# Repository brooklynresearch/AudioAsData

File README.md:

Vibrotextiles
=============
This repo is for all hardware and firmware associated with the vibrotextiles.
This is still a work in progress and will be updated as future commits occur.

Firmware
--------
This folder contains all the firmware, libraries, and testing instructions for the vibrotextiles

Javascript
----------
This folder contains a simple web based tester for APSK.

Hardware
--------
This folder contains all the schematics, layouts, components, production files, and artwork needed for the vibrotextiles.

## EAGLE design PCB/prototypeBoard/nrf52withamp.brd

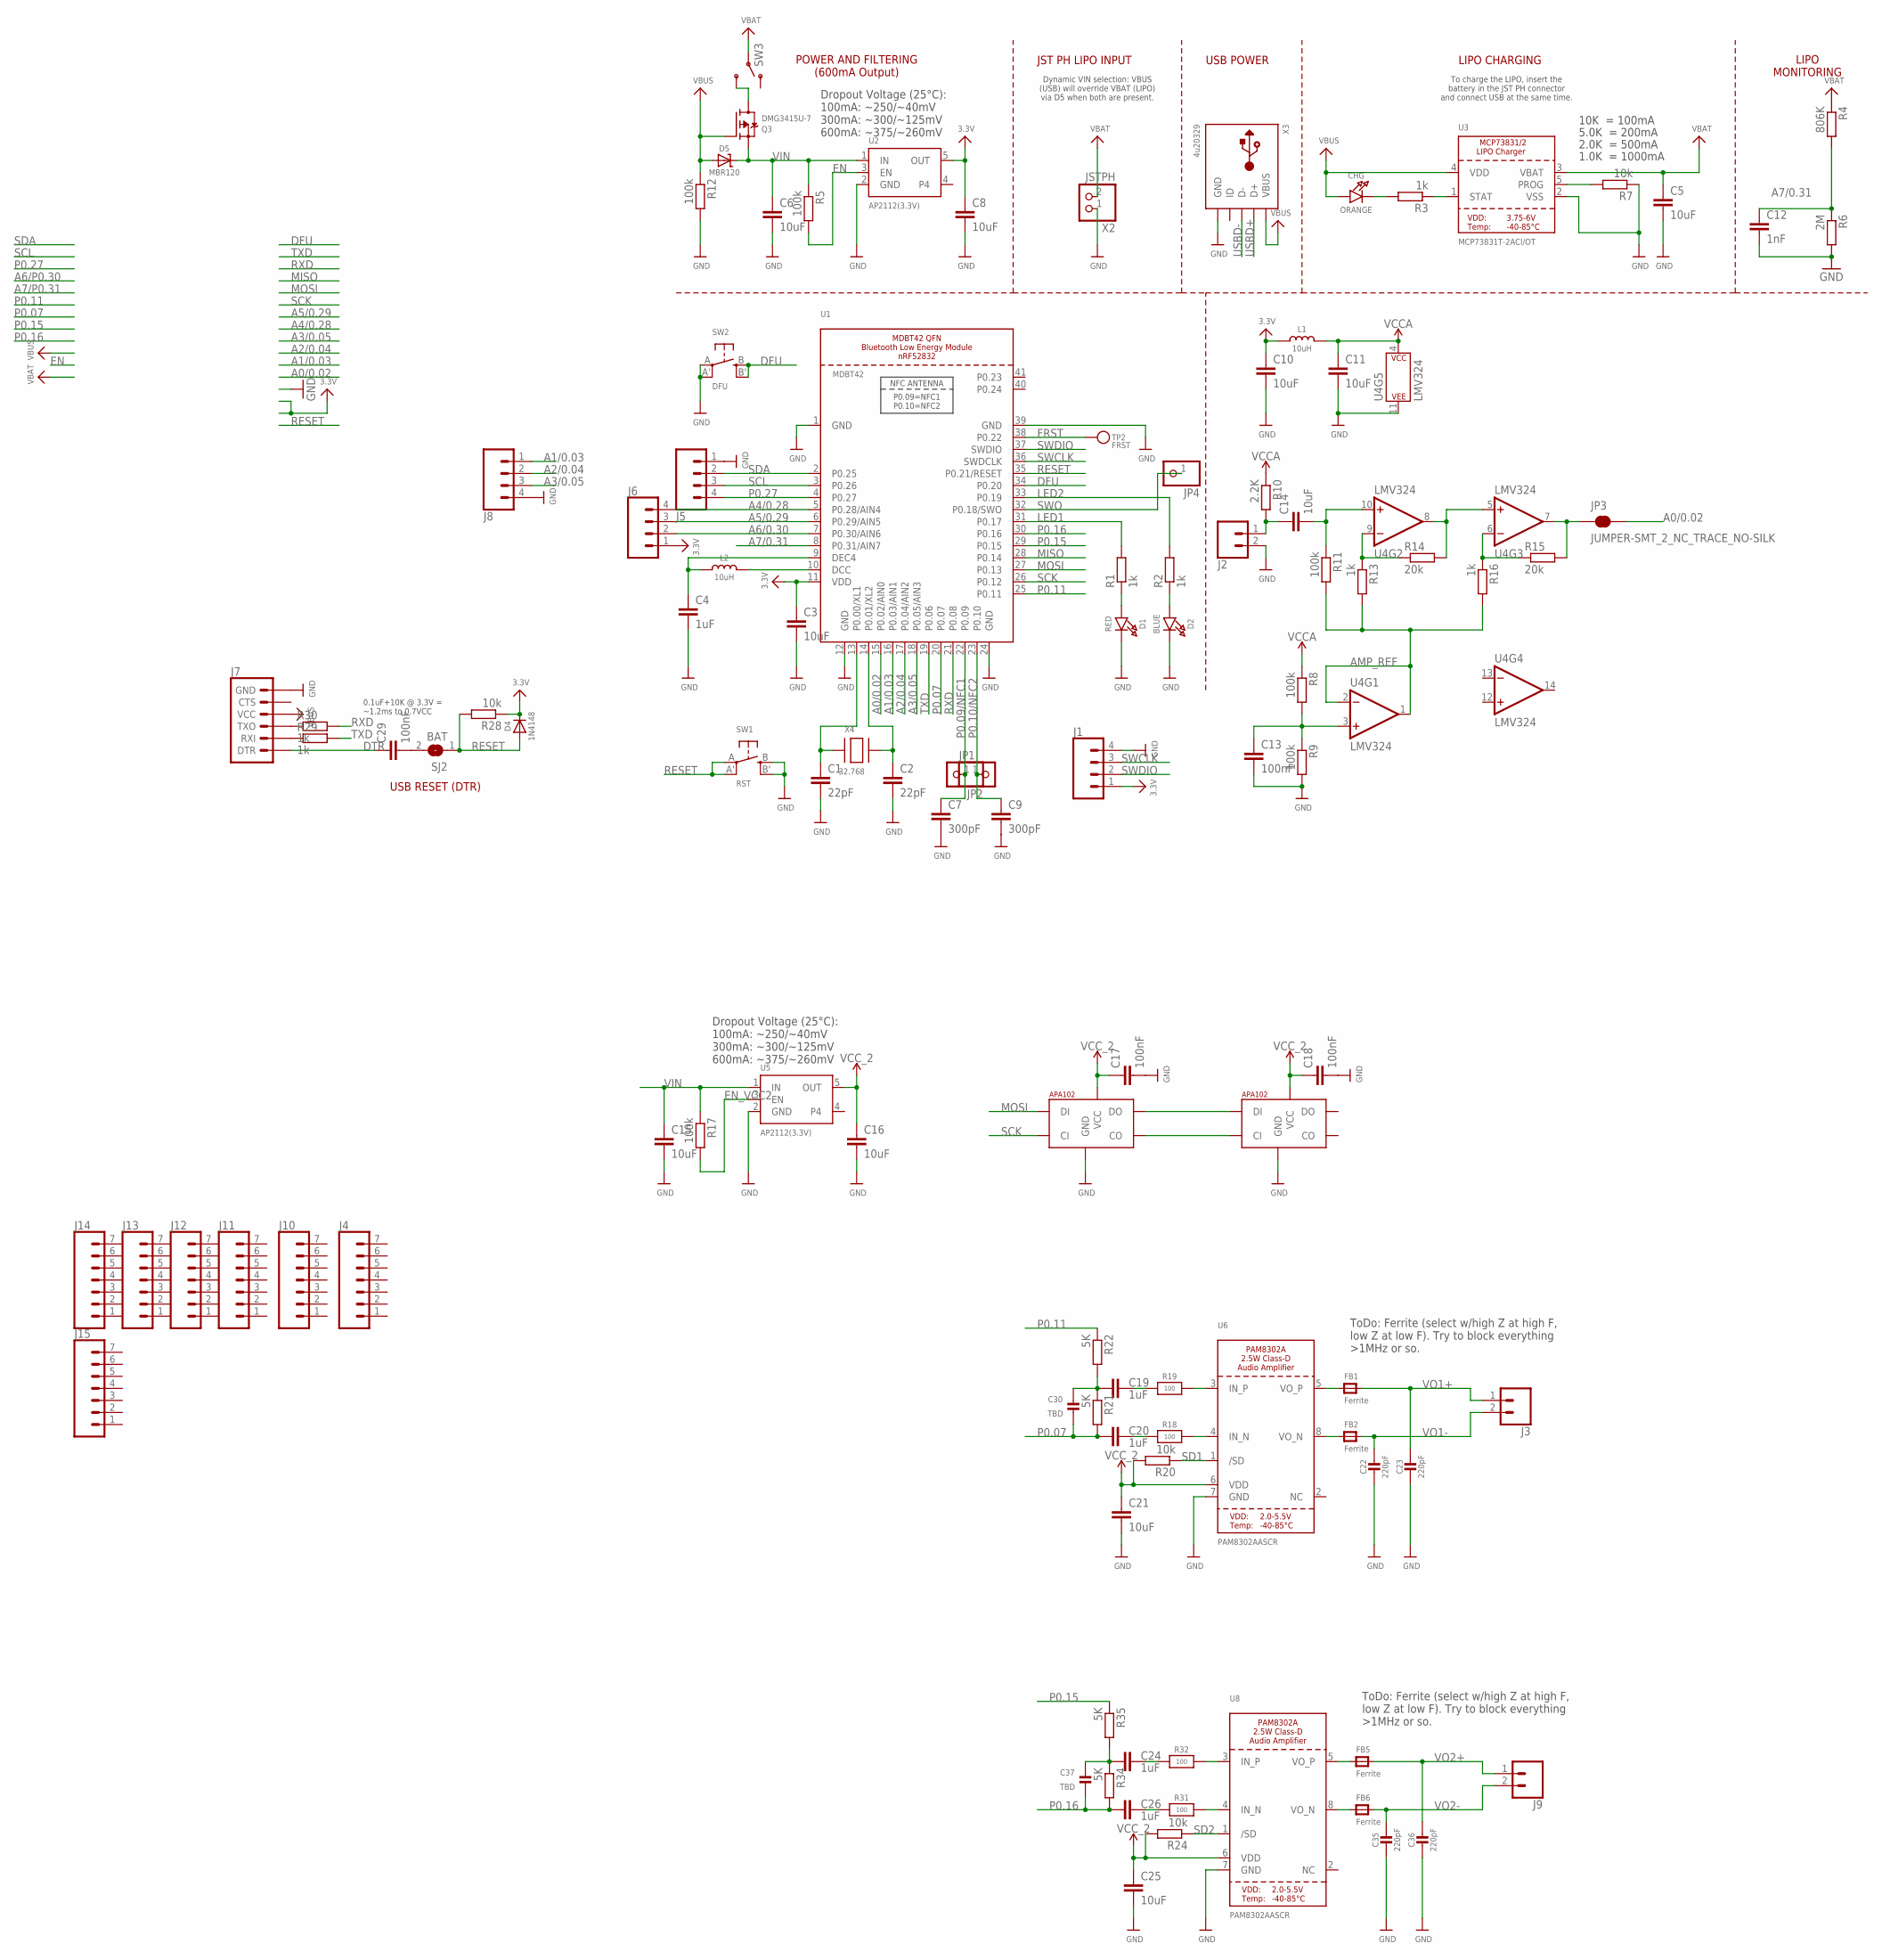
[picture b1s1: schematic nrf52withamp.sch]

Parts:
C1, C2: 22pF; C0805; LCSC C1836
C3, C5, C6, C8, C10, C11, C14, C15, C16, C21, C25: 10uF; C0805; LCSC C1713
C4, C19, C20, C24, C26: 1uF; C0805; LCSC C29822
C7, C9: 300pF; C0805; LCSC C1735
C12: 1nF; C0805; LCSC C16005
C13, C17, C18, C29: 100nF; C0805; LCSC C28378
C22, C23, C35, C36: 220pF; 0805-NO; LCSC C46326
C30, C37: TBD; 0805-NO
CHG: ORANGE; CHIPLED_0805_NOOUTLINE; LCSC C154481
D1: RED; CHIPLED_0805_NOOUTLINE; LCSC C72037
D2: BLUE; CHIPLED_0805_NOOUTLINE; LCSC C2293
D4: 1N4148; SOD-323; LCSC C99332
D5: MBR120; SOD-123; LCSC C130880
FB1, FB2, FB5, FB6: Ferrite; _0805; LCSC C12389
J1: CONN_04SMD; 1X04_SMD_RA_MALE
J2, J3, J9: CONN_02; 1X02
J4, J10, J11, J12, J13, J14, J15: CONN_07; 1X07
J5, J6, J8: CONN_041.27MM; 1X04_1.27MM
J7: 6_PIN_SERIAL_TARGETRA_SMT; 6_PIN_SERIAL_TARGET_SIDE_RA_SMT
JP1, JP2, JP4: HEADER-1X12MM; 1X01_2MM
JP3: JUMPER-SMT_2_NC_TRACE_NO-SILK; SMT-JUMPER_2_NC_TRACE_NO-SILK
L1, L2: 10uH; 0805-NO@1; LCSC C112611
Q3: DMG3415U-7; SOT23-R; LCSC C10487
R1, R2, R3, R13, R16, R29, R30: 1k; R0805; LCSC C101404
R4: 806K; R0805; LCSC C104516
R5, R8, R9, R11, R12, R17: 100k; R0805; LCSC C103905
R6: 2M; R0805; LCSC C26112
R7, R20, R24, R28: 10k; R0805; LCSC C84376
R10: 2.2K; R0805; LCSC C101970
R14, R15: 20k; R0805; LCSC C101548
R18, R19, R31, R32: 100; 0805-NO; LCSC C153166
R21, R22, R34, R35: 5K; R0805; LCSC C84375
SJ2: BAT; SOLDERJUMPER_CLOSEDWIRE
SW1: RST; BTN_KMR2_4.6X2.8; DIGIKEY CKN10246CT-ND
SW2: DFU; BTN_KMR2_4.6X2.8; DIGIKEY CKN10246CT-ND
SW3: SWITCH_SPDT; KPS-1290; LCSC C128955
TP2: FRST; PAD-1.5X2.0
U1: MDBT42; BLE_MODULE_RAYTAC_MDBT42; DIGIKEY 1597-1434-ND
U2, U5: AP2112(3.3V); SOT23-5; LCSC C51118
U3: MCP73831T-2ACI/OT; SOT23-5; LCSC C14879
U4: LMV324; SO14; LCSC C7974
U6, U8: PAM8302AASCR; MSOP8_0.65MM; LCSC C113367
U$45, U$51: APA1022020; APA102_2020; DIGIKEY 1568-1826-ND
X2: JSTPH; JSTPH2; DIGIKEY 455-1749-1-ND
X3: 4u20329; 4UCONN_20329_V2; LCSC C91146
X4: 32.768; XTAL3215; LCSC C48615

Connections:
3.3V: C3.1, C8.1, C10.1, D4.C, J1.1, J6.1, L1.1, R28.1, U1.11 (VDD), U2.5 (OUT)
A0/0.02: JP3.2, U1.15 (P0.02/AIN0)
A1/0.03: J8.1, U1.16 (P0.03/AIN1)
A2/0.04: J8.2, U1.17 (P0.04/AIN2)
A3/0.05: J8.3, U1.18 (P0.05/AIN3)
A4/0.28: J6.4, U1.5 (P0.28/AIN4)
A5/0.29: J6.3, U1.6 (P0.29/AIN5)
A6/0.30: J6.2, U1.7 (P0.30/AIN6)
A7/0.31: C12.1, R4.2, R6.1, U1.8 (P0.31/AIN7)
AMP_REF: R11.2, R13.2, R16.2, U4.1 (OUT), U4.2 (-IN)
CO1: U$45.CL_OUT (CO), U$51.C_IN (CI)
DFU: SW2.B (S), SW2.B' (S1), U1.34 (P0.20)
DTR: C29.1, J7.1 (DTR)
EN: R5.2, U2.3 (EN)
EN_VCC2: R17.2, U5.3 (EN)
FRST: TP2.P$1, U1.38 (P0.22)
GND: C1.2, C2.2, C3.2, C4.2, C5.2, C6.2, C7.2, C8.2, C9.2, C10.2, C11.2, C12.2, C13.2, C15.2, C16.2, C17.2, C18.2, C21.2, C22.2, C23.2, C25.2, C35.2, C36.2, D1.C, D2.C, J1.4, J2.2, J5.1, J7.6 (GND), J8.4, R6.2, R7.1, R9.2, R12.2, SW1.B (S), SW1.B' (S1), SW2.A, SW2.A' (P1), U1.1 (GND), U1.12 (GND), U1.24 (GND), U1.39 (GND), U2.2 (GND), U3.2 (VSS), U4.11 (P$V-), U5.2 (GND), U6.7 (GND), U8.7 (GND), U$45.GND, U$51.GND, X2.1, X3.BASE@1 (GND), X3.BASE@2 (GND), X3.GND, X3.SPRT@1 (GND), X3.SPRT@2 (GND), X3.SPRT@3 (GND), X3.SPRT@4 (GND)
LED1: R1.2, U1.31 (P0.17)
LED2: R2.2, U1.33 (P0.19)
MISO: U1.28 (P0.14)
MOSI: U1.27 (P0.13), U$45.D_IN (DI)
unnamed: C1.1, U1.13 (P0.00/XL1), X4.P$1
unnamed: C2.1, U1.14 (P0.01/XL2), X4.P$2
unnamed: L2.2, U1.10 (DCC)
unnamed: CHG.C, R3.2
unnamed: D1.A, R1.1
unnamed: C13.1, R8.2, R9.1, U4.3 (+IN)
unnamed: D2.A, R2.1
unnamed: C4.1, L2.1, U1.9 (DEC4)
unnamed: R3.1, U3.1 (STAT)
unnamed: R7.2, U3.5 (PROG)
unnamed: C14.1, J2.1, R10.2
unnamed: C14.2, R11.1, U4.10 (+IN)
unnamed: C29.2, SJ2.2
unnamed: U$45.D_OUT (DO), U$51.D_IN (DI)
unnamed: R13.1, R14.1, U4.9 (-IN)
unnamed: R14.2, U4.5 (+IN), U4.8 (OUT)
unnamed: R15.1, R16.1, U4.6 (-IN)
unnamed: JP3.1, R15.2, U4.7 (OUT)
unnamed: R18.2, U6.4 (IN_N)
unnamed: R19.2, U6.3 (IN_P)
unnamed: C20.2, R18.1
unnamed: FB2.1, U6.8 (VO_N)
unnamed: FB1.1, U6.5 (VO_P)
unnamed: C19.2, R19.1
unnamed: C19.1, C30.1, R21.1, R22.2
unnamed: Q3.3 (D), SW3.S
unnamed: J7.3 (RXI), R29.1
unnamed: J7.2 (TXO), R30.1
unnamed: R31.2, U8.4 (IN_N)
unnamed: R32.2, U8.3 (IN_P)
unnamed: C26.2, R31.1
unnamed: FB6.1, U8.8 (VO_N)
unnamed: FB5.1, U8.5 (VO_P)
unnamed: C24.2, R32.1
unnamed: C24.1, C37.1, R34.1, R35.2
P0.07: C20.1, C30.2, R21.2, U1.20 (P0.07)
P0.09/NFC1: C7.1, JP2.1, U1.22 (P0.09)
P0.10/NFC2: C9.1, JP1.1, U1.23 (P0.10)
P0.11: R22.1, U1.25 (P0.11)
P0.15: R35.1, U1.29 (P0.15)
P0.16: C26.1, C37.2, R34.2, U1.30 (P0.16)
P0.27: J5.4, U1.4 (P0.27)
RESET: D4.A, R28.2, SJ2.1, SW1.A, SW1.A' (P1), U1.35 (P0.21/RESET)
RXD: R30.2, U1.21 (P0.08)
SCK: U1.26 (P0.12), U$45.C_IN (CI)
SCL: J5.3, U1.3 (P0.26)
SD1: R20.1, U6.1 (/SD)
SD2: R24.1, U8.1 (/SD)
SDA: J5.2, U1.2 (P0.25)
SWCLK: J1.3, U1.36 (SWDCLK)
SWDIO: J1.2, U1.37 (SWDIO)
SWO: JP4.1, U1.32 (P0.18/SWO)
TXD: R29.2, U1.19 (P0.06)
USBD+: X3.D+
USBD-: X3.D-
VBAT: C5.1, R4.1, SW3.P, U3.3 (VBAT), X2.2
VBUS: CHG.A, D5.A, J7.4 (VCC), Q3.1 (G), R12.1, U3.4 (VDD), X3.VBUS
VCCA: C11.1, L1.2, R8.1, R10.1, U4.4 (P$V+)
VCC_2: C16.1, C17.1, C18.1, C21.1, C25.1, R20.2, R24.2, U5.5 (OUT), U6.6 (VDD), U8.6 (VDD), U$45.V_CC (VCC), U$51.V_CC (VCC)
VIN: C6.1, C15.1, D5.C, Q3.2 (S), R5.1, R17.1, U2.1 (IN), U5.1 (IN)
VO1+: C23.1, FB1.2, J3.1
VO1-: C22.1, FB2.2, J3.2
VO2+: C36.1, FB5.2, J9.1
VO2-: C35.1, FB6.2, J9.2

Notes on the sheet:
10K = 100mA
5.0K = 200mA
2.0K = 500mA
1.0K = 1000mA
LIPO CHARGING
LIPO MONITORING
To charge the LIPO, insert the battery in the JST PH connector and connect USB at the same time.
POWER AND FILTERING (600mA Output)
JST PH LIPO INPUT
Dynamic VIN selection: VBUS (USB) will override VBAT (LIPO) via D5 when both are present.
Dropout Voltage (25°C): 100mA: ~250/~40mV 300mA: ~300/~125mV 600mA: ~375/~260mV
USB POWER
ToDo: Ferrite (select w/high Z at high F, low Z at low F). Try to block everything >1MHz or so.
USB RESET (DTR)
0.1uF+10K @ 3.3V = ~1.2ms to 0.7VCC

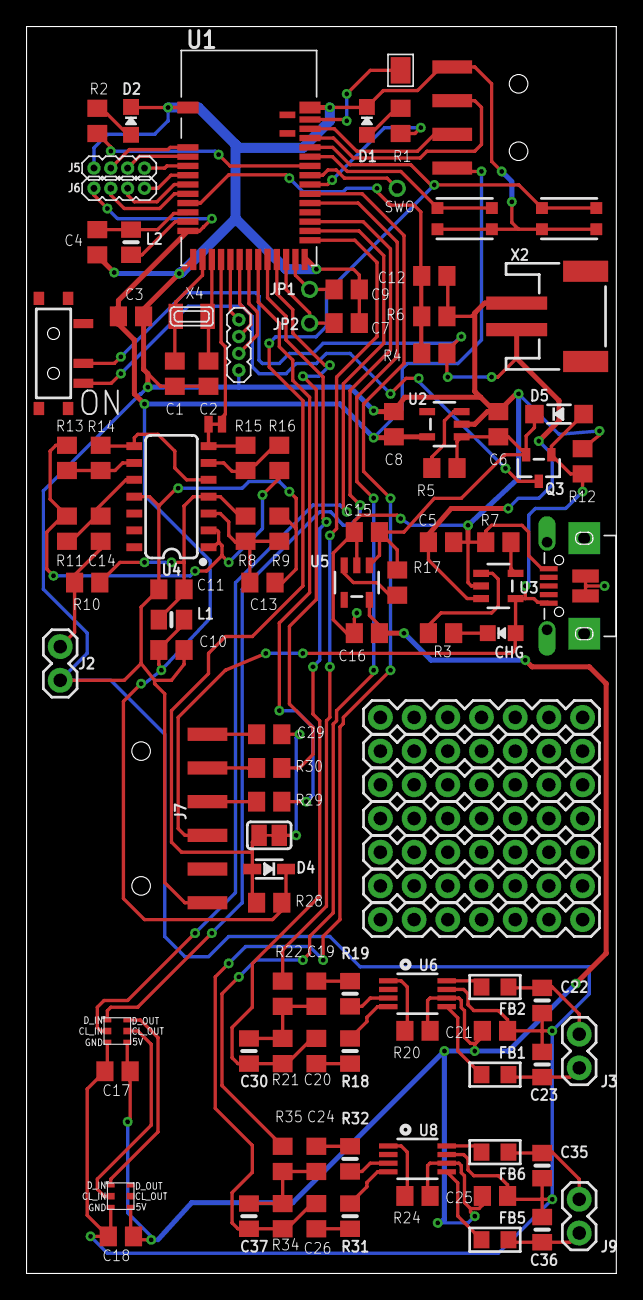
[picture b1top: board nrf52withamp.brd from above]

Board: 2 copper layers, 44.5 x 94.0 mm, 109 parts (0 on the bottom side), 82 nets.

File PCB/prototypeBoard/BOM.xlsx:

Qty | Value | Device | Package | Parts | Description | DIGIKEY | LCSC | PROD_ID | SF_ID | SPICEPREFIX | VALUE
4 | 100 | RESISTOR0805_NOOUTLINE | 0805-NO | R18, R19, R31, R32 | Resistors |  | C153166
6 | 100k | R-EU_R0805 | R0805 | R5, R8, R9, R11, R12, R17 | RESISTOR, European symbol |  | C103905 |  |  | R
4 | 100nF | C-EUC0805 | C0805 | C13, C17, C18, C29 | CAPACITOR, European symbol |  | C28378 |  |  | C
4 | 10k | R-EU_R0805 | R0805 | R7, R20, R24, R28 | RESISTOR, European symbol |  | C84376 |  |  | R
11 | 10uF | C-EUC0805 | C0805 | C3, C5, C6, C8, C10, C11, C14, C15, C16, C21, C25 | CAPACITOR, European symbol |  | C1713 |  |  | C
2 | 10uH | INDUCTOR0805-NO | 0805-NO@1 | L1, L2 | Inductors |  | C112611
1 | 1N4148 | DIODESOD-323 | SOD-323 | D4 | Diode |  | C99332
7 | 1k | R-EU_R0805 | R0805 | R1, R2, R3, R13, R16, R29, R30 | RESISTOR, European symbol |  | C101404 |  |  | R
1 | 1nF | C-EUC0805 | C0805 | C12 | CAPACITOR, European symbol |  | C16005 |  |  | C
5 | 1uF | C-EUC0805 | C0805 | C4, C19, C20, C24, C26 | CAPACITOR, European symbol |  | C29822 |  |  | C
1 | 2.2K | R-EU_R0805 | R0805 | R10 | RESISTOR, European symbol |  | C101970 |  |  | R
2 | 20k | R-EU_R0805 | R0805 | R14, R15 | RESISTOR, European symbol |  | C101548 |  |  | R
4 | 220pF | CAP_CERAMIC0805-NOOUTLINE | 0805-NO | C22, C23, C35, C36 | Ceramic Capacitors |  | C46326
2 | 22pF | C-EUC0805 | C0805 | C1, C2 | CAPACITOR, European symbol |  | C1836 |  |  | C
1 | 2M | R-EU_R0805 | R0805 | R6 | RESISTOR, European symbol |  | C26112 |  |  | R
2 | 300pF | C-EUC0805 | C0805 | C7, C9 | CAPACITOR, European symbol |  | C1735 |  |  | C
1 | 32.768000000000001 | XTAL-3.2X1.5 | XTAL3215 | X4 | Low cost SMT crystals, no capacitors included |  | C48615
1 | 4u20329 | USB_MICRO_20329_V2 | 4UCONN_20329_V2 | X3 | USB Connectors |  | C91146
4 | 5K | R-EU_R0805 | R0805 | R21, R22, R34, R35 | RESISTOR, European symbol |  | C84375 |  |  | R
1 | 806K | R-EU_R0805 | R0805 | R4 | RESISTOR, European symbol |  | C104516 |  |  | R
2 | AP2112(3.3V) | VREG_SOT23-5 | SOT23-5 | U2, U5 | SOT23-5 Fixed Voltage Regulators |  | C51118
2 | APA1022020 | APA1022020 | APA102_2020 | U$45, U$51 | APA102C 5050 RGB LED | 1568-1826-ND
1 | BLUE | LED0805_NOOUTLINE | CHIPLED_0805_NOOUTLINE | D2 | LED |  | C2293
1 | DFU | SWITCH_TACT_SMT4.6X2.8 | BTN_KMR2_4.6X2.8 | SW2 | SMT Tact Switches | CKN10246CT-ND
1 | DMG3415U-7 | MOSFET-P | SOT23-R | Q3 | P-Channel Mosfet |  | C10487
1 | FRST | TESTPOINT1.5X2.0MM_NOCREAM | PAD-1.5X2.0 | TP2 | Test Point
4 | Ferrite | FERRITE_0805 | _0805 | FB1, FB2, FB5, FB6 | Ferrite Bead |  | C12389
1 | JSTPH | CON_JST_PH_2PIN | JSTPH2 | X2 | JST 2-Pin Right-Angle Connector | 455-1749-1-ND
1 | LMV324 | LMV324 | SO14 | U4 | IC LMV324 Quad Op Amp |  | C7974 | IC-08227 |  |  | LMV324
1 | MBR120 | DIODE-SCHOTTKYSOD-123 | SOD-123 | D5 |  |  | C130880
1 | MCP73831T-2ACI/OT | MCP73831/2 | SOT23-5 | U3 | MCP73831/2 LIPO Charger |  | C14879
1 | MDBT42 | NRF52832_MODULE_MDBT42 | BLE_MODULE_RAYTAC_MDBT42 | U1 | MDBT42 - BLE Module (nRF52832 QFN) | 1597-1434-ND
1 | ORANGE | LED0805_NOOUTLINE | CHIPLED_0805_NOOUTLINE | CHG | LED |  | C154481
2 | PAM8302AASCR | AUDIOAMP_PAM8302A | MSOP8_0.65MM | U6, U8 | PAM8302A - 2.5W Class-D Mono Audio Amplifier |  | C113367
1 | RED | LED0805_NOOUTLINE | CHIPLED_0805_NOOUTLINE | D1 | LED |  | C72037
1 | RST | SWITCH_TACT_SMT4.6X2.8 | BTN_KMR2_4.6X2.8 | SW1 | SMT Tact Switches | CKN10246CT-ND
1 | SWITCH_SPDT | SWITCH_SPDT | KPS-1290 | SW3 | SWCH-10651 |  | C128955 | SWCH-10651
2 | TBD | CAP_CERAMIC0805-NOOUTLINE | 0805-NO | C30, C37 | Ceramic Capacitors

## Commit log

2018-03-05 Initial Commit
    Initial Commit for Vibrotextiles
2018-03-08 add board
2018-03-08 move files
2018-03-08 update code
2018-03-11 add PCB
2018-03-15 update board
2018-03-15 add bom and gerber
2018-03-26 add fix
2018-03-29 change pins to PCB pins
2018-03-29 add measurement

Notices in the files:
parts and their libraries:
microbuilder: This work is placed in the public domain, and may be freely used for commercial and non-commercial work with the following conditions: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
SparkFun-Connectors: Licensing: Creative Commons ShareAlike 4.0 International - https://creativecommons.org/licenses/by-sa/4.0
